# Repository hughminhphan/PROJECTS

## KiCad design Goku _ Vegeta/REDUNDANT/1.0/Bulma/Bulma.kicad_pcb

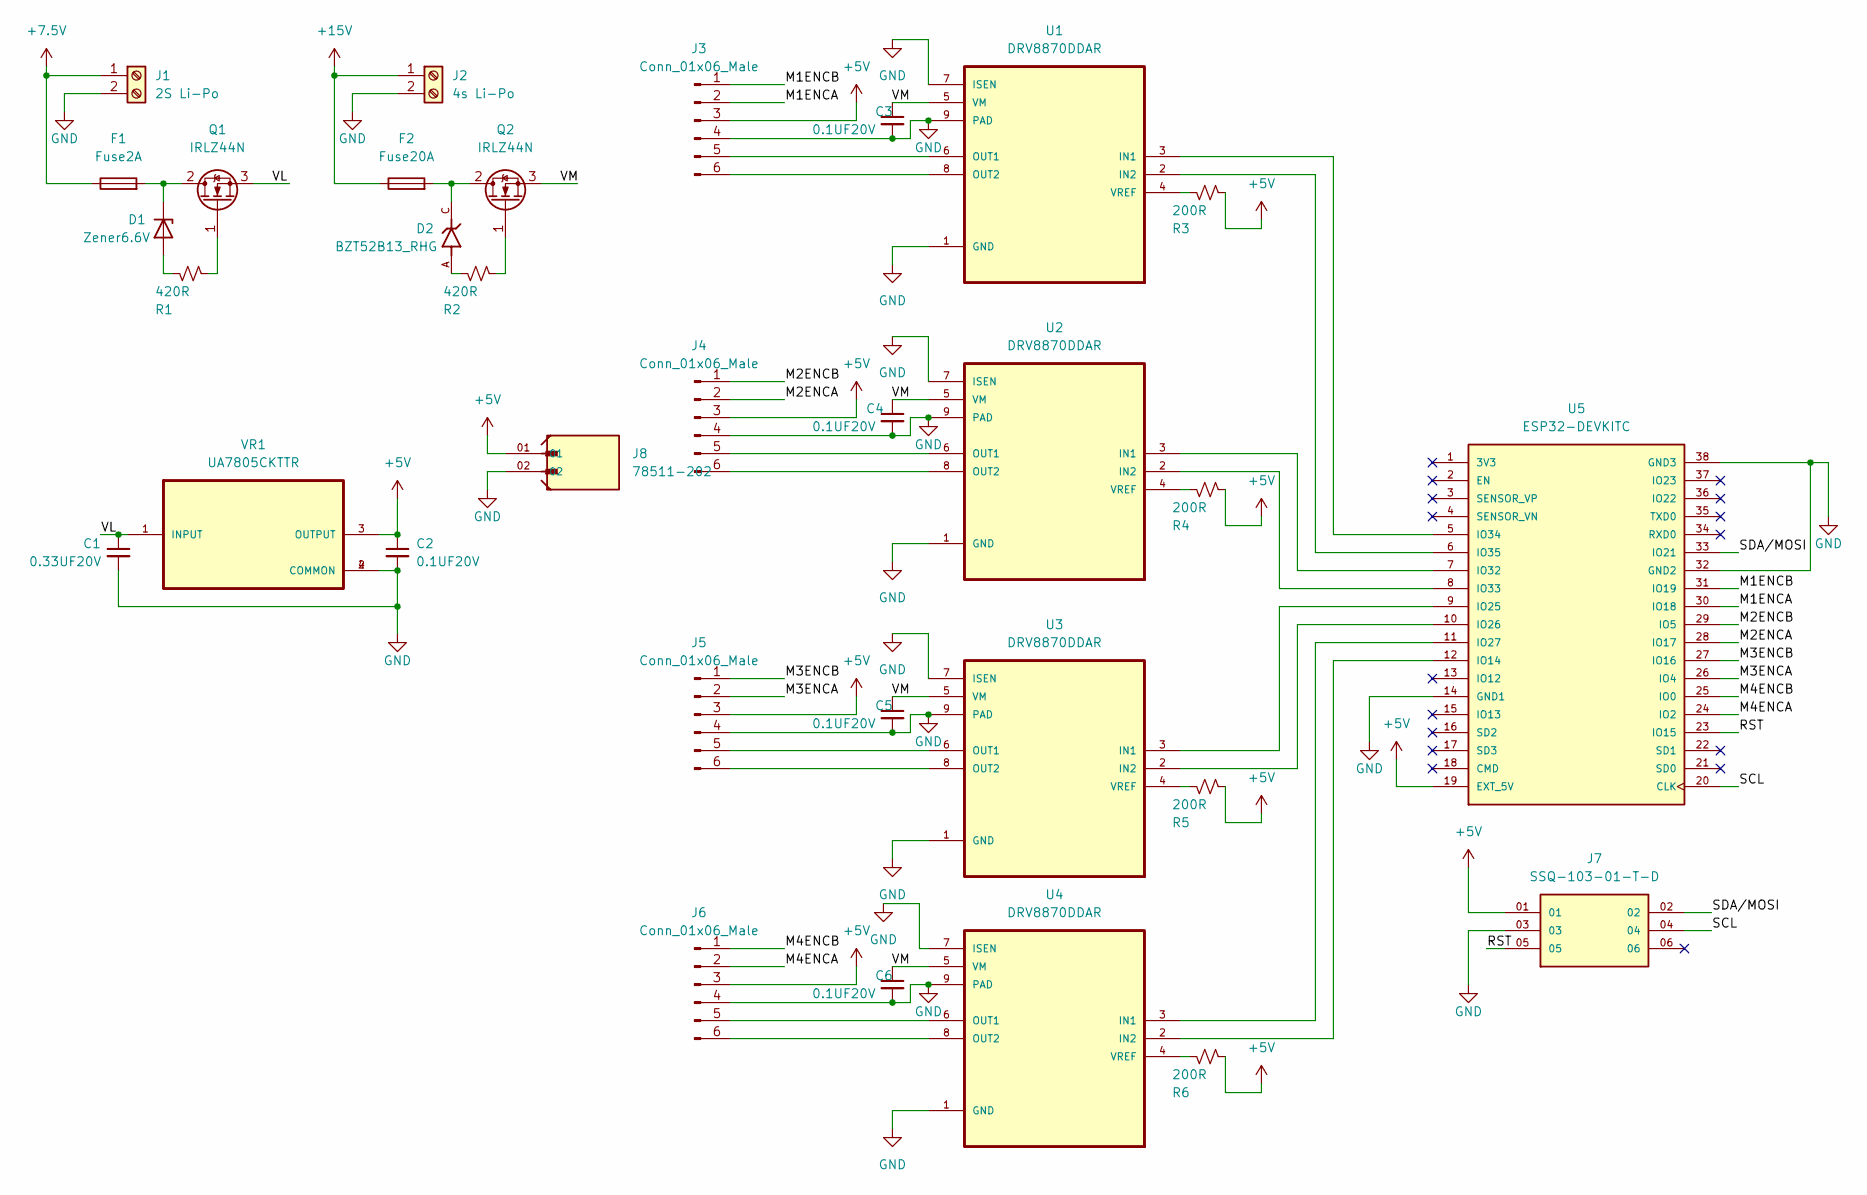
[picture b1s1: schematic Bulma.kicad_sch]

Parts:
C1: 0.33UF20V; C_0201_0603Metric
C2, C3, C4, C5, C6: 0.1UF20V; C_0402_1005Metric
D1: Zener6.6V; SODFL4725X110N
D2: BZT52B13_RHG; DIO_BZT52B13_RHG; PARTREV F15
F1: Fuse2A; FUSC1608X60N
F2: Fuse20A; FUSC3215X85N
J1: 2S Li-Po; 2 Position Wire to Board Terminal Block Horizontal with Boa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
J2: 4s Li-Po; 2 Position Wire to Board Terminal Block Horizontal with Boa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
J3, J5, J6: Conn_01x06_Male; PinSocket_1x06_P2.54mm_Vertical
J4: Conn_01x06_Male; PinHeader_1x06_P2.54mm_Vertical
J7: SSQ-103-01-T-D; SAMTEC_SSQ-103-01-T-D; PARTREV R
J8: 78511-202; AMPHENOL_78511-202; PARTREV DF
Q1, Q2: IRLZ44N; TO-263-2
R1, R2: 420R; R_0805_2012Metric
R3, R4, R5, R6: 200R; R_1206_3216Metric
U1, U2, U3, U4: DRV8870DDAR; VREG_LM5017MR_NOPB
U5: ESP32-DEVKITC; MODULE_ESP32-DEVKITC; PARTREV N/A
VR1: UA7805CKTTR; TO254P1524X483-4N

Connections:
+5V: C2.1, J3.3, J4.3, J5.3, J6.3, J7.01, J8.01, R3.2, R4.2, R5.2, R6.2, U5.19 (EXT_5V), VR1.3 (OUTPUT)
+7.5V: F1.1, J1.1
+15V: F2.1, J2.1
/M1ENCA: J3.2, U5.30 (IO18)
/M1ENCB: J3.1, U5.31 (IO19)
/M2ENCA: J4.2, U5.28 (IO17)
/M2ENCB: J4.1, U5.29 (IO5)
/M3ENCA: J5.2, U5.26 (IO4)
/M3ENCB: J5.1, U5.27 (IO16)
/M4ENCA: J6.2, U5.24 (IO2)
/M4ENCB: J6.1, U5.25 (IO0)
/RST: J7.05, U5.23 (IO15)
/SCL: J7.04, U5.20 (CLK)
/SDA/MOSI: J7.02, U5.33 (IO21)
/VL: C1.1, Q1.3 (S), VR1.1 (INPUT)
/VM: C3.1, C4.1, C5.1, C6.1, Q2.3 (S), U1.5 (VM), U2.5 (VM), U3.5 (VM), U4.5 (VM)
GND: C1.2, C2.2, C3.2, C4.2, C5.2, C6.2, J1.2, J2.2, J3.4, J4.4, J5.4, J6.4, J7.03, J8.02, U1.1 (GND), U1.7 (ISEN), U1.9 (PAD), U2.1 (GND), U2.7 (ISEN), U2.9 (PAD), U3.1 (GND), U3.7 (ISEN), U3.9 (PAD), U4.1 (GND), U4.7 (ISEN), U4.9 (PAD), U5.14 (GND1), U5.32 (GND2), U5.38 (GND3), VR1.2 (COMMON), VR1.4 (COMMON)
unnamed: D1.1 (K), F1.2, Q1.2 (D)
unnamed: D1.2 (A), R1.1
unnamed: D2.A, R2.1
unnamed: D2.C, F2.2, Q2.2 (D)
unnamed: J3.5, U1.6 (OUT1)
unnamed: J3.6, U1.8 (OUT2)
unnamed: J4.5, U2.6 (OUT1)
unnamed: J4.6, U2.8 (OUT2)
unnamed: J5.5, U3.6 (OUT1)
unnamed: J5.6, U3.8 (OUT2)
unnamed: J6.5, U4.6 (OUT1)
unnamed: J6.6, U4.8 (OUT2)
unnamed: Q1.1 (G), R1.2
unnamed: Q2.1 (G), R2.2
unnamed: R3.1, U1.4 (VREF)
unnamed: R4.1, U2.4 (VREF)
unnamed: R5.1, U3.4 (VREF)
unnamed: R6.1, U4.4 (VREF)
unnamed: U1.2 (IN2), U5.6 (IO35)
unnamed: U1.3 (IN1), U5.5 (IO34)
unnamed: U2.2 (IN2), U5.8 (IO33)
unnamed: U2.3 (IN1), U5.7 (IO32)
unnamed: U3.2 (IN2), U5.10 (IO26)
unnamed: U3.3 (IN1), U5.9 (IO25)
unnamed: U4.2 (IN2), U5.12 (IO14)
unnamed: U4.3 (IN1), U5.11 (IO27)

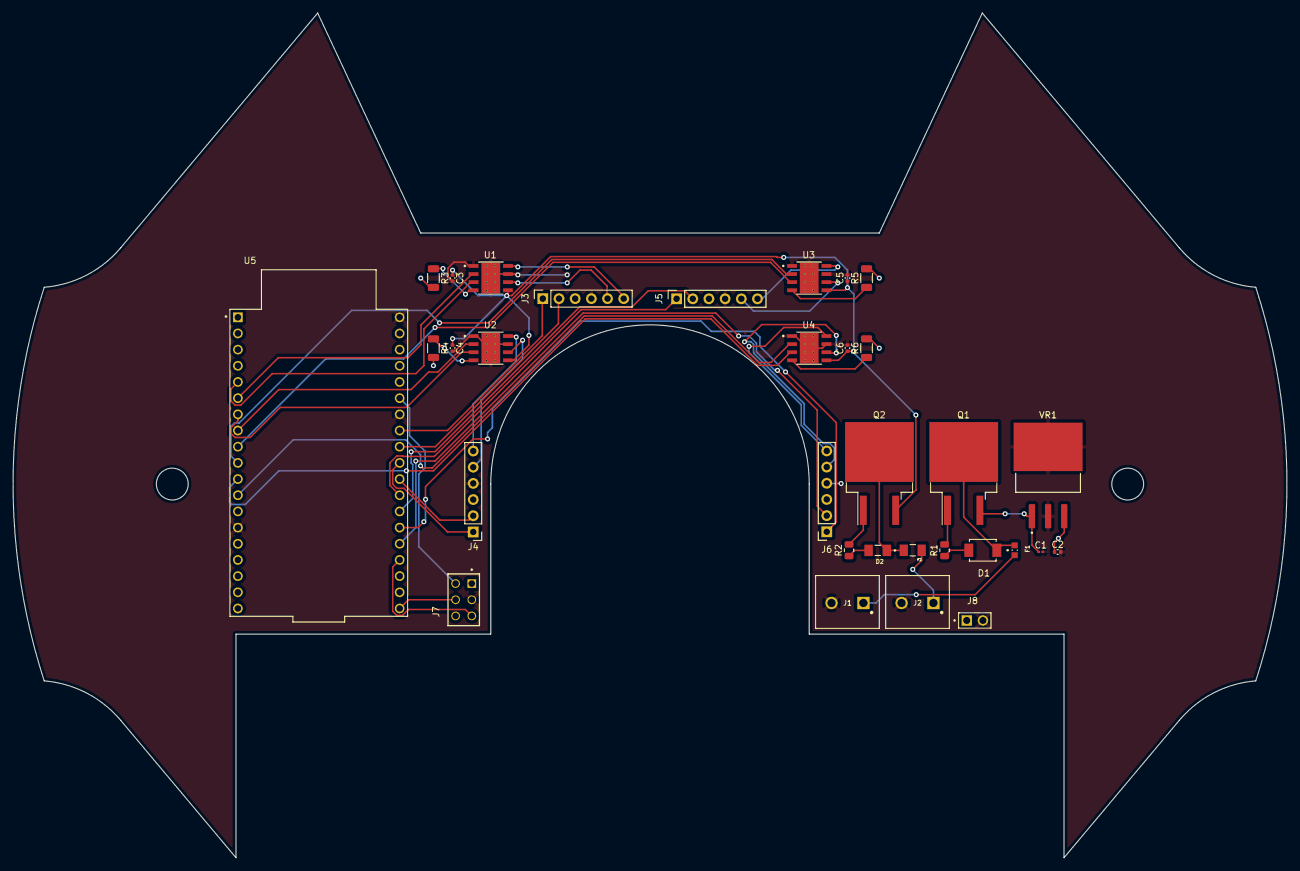
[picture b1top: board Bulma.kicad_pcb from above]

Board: 2 copper layers, 200.0 x 132.6 mm, 32 parts (0 on the bottom side), 43 nets.

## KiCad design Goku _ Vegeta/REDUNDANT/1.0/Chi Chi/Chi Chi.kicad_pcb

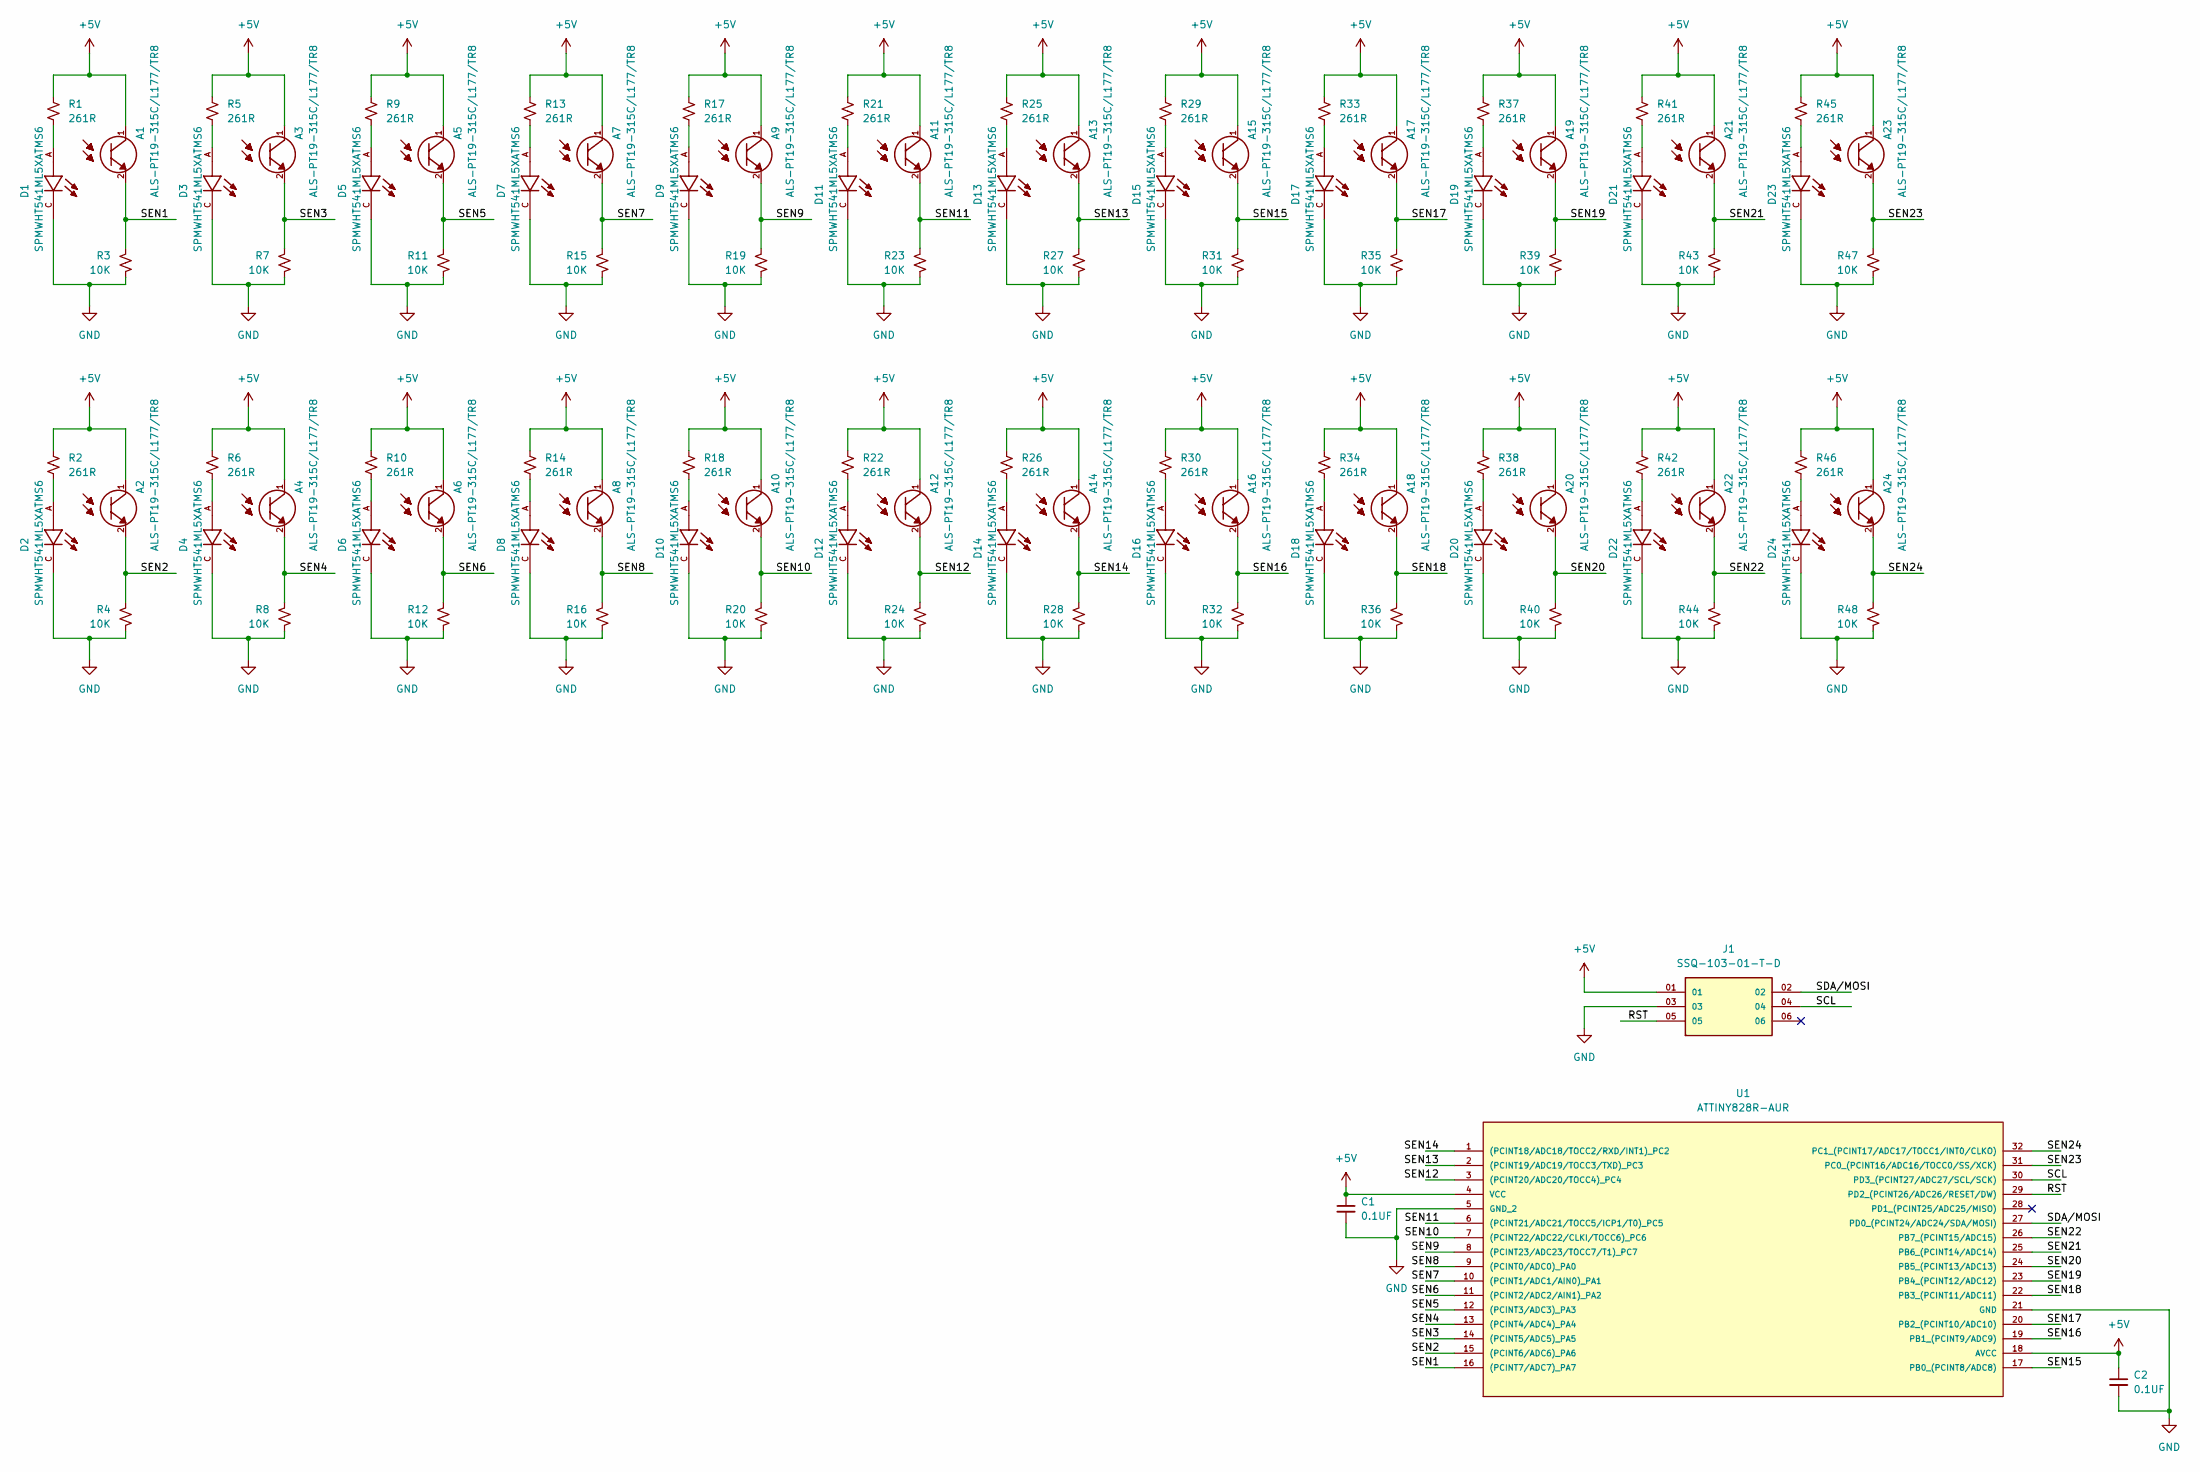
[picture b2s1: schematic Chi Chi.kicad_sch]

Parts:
A1, A2, A3, A4, A5, A6, A7, A8, A9, A10, A11, A12, A13, A14, A15, A16, A17, A18, A19, A20, A21, A22, A23, A24: ALS-PT19-315C/L177/TR8; XDCR_ALS-PT19-315C_L177_TR8; PARTREV 5
C1, C2: 0.1UF; C_0805_2012Metric_Pad1.18x1.45mm_HandSolder
D1, D2, D3, D4, D5, D6, D7, D8, D9, D10, D11, D12, D13, D14, D15, D16, D17, D18, D19, D20, D21, D22, D23, D24: SPMWHT541ML5XATMS6; LED_SPMWHT541MP5WAPKS4; PARTREV 8.3
J1: SSQ-103-01-T-D; SAMTEC_SSQ-103-01-T-D; PARTREV R
R1, R2, R5, R6, R9, R10, R13, R14, R17, R18, R21, R22, R25, R26, R29, R30, R33, R34, R37, R38, R41, R42, R45, R46: 261R; R_0805_2012Metric_Pad1.20x1.40mm_HandSolder
R3, R4, R7, R8, R11, R12, R15, R16, R19, R20, R23, R24, R27, R28, R31, R32, R35, R36, R39, R40, R43, R44, R47, R48: 10K; R_0805_2012Metric_Pad1.20x1.40mm_HandSolder
U1: ATTINY828R-AUR; TQFP32_9X9_MCH; MANUFACTURER_PART_NUMBER ATTINY828R-AUR

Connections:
+5V: A1.1, A2.1, A3.1, A4.1, A5.1, A6.1, A7.1, A8.1, A9.1, A10.1, A11.1, A12.1, A13.1, A14.1, A15.1, A16.1, A17.1, A18.1, A19.1, A20.1, A21.1, A22.1, A23.1, A24.1, C1.1, C2.1, J1.01, R1.1, R2.1, R5.1, R6.1, R9.1, R10.1, R13.1, R14.1, R17.1, R18.1, R21.1, R22.1, R25.1, R26.1, R29.1, R30.1, R33.1, R34.1, R37.1, R38.1, R41.1, R42.1, R45.1, R46.1, U1.4 (VCC), U1.18 (AVCC)
/RST: J1.05, U1.29 (PD2_(PCINT26/ADC26/RESET/DW))
/SCL: J1.04, U1.30 (PD3_(PCINT27/ADC27/SCL/SCK))
/SDA/MOSI: J1.02, U1.27 (PD0_(PCINT24/ADC24/SDA/MOSI))
/SEN1: A1.2, R3.2, U1.16 ((PCINT7/ADC7)_PA7)
/SEN2: A2.2, R4.2, U1.15 ((PCINT6/ADC6)_PA6)
/SEN3: A3.2, R7.2, U1.14 ((PCINT5/ADC5)_PA5)
/SEN4: A4.2, R8.2, U1.13 ((PCINT4/ADC4)_PA4)
/SEN5: A5.2, R11.2, U1.12 ((PCINT3/ADC3)_PA3)
/SEN6: A6.2, R12.2, U1.11 ((PCINT2/ADC2/AIN1)_PA2)
/SEN7: A7.2, R15.2, U1.10 ((PCINT1/ADC1/AIN0)_PA1)
/SEN8: A8.2, R16.2, U1.9 ((PCINT0/ADC0)_PA0)
/SEN9: A9.2, R19.2, U1.8 ((PCINT23/ADC23/TOCC7/T1)_PC7)
/SEN10: A10.2, R20.2, U1.7 ((PCINT22/ADC22/CLKI/TOCC6)_PC6)
/SEN11: A11.2, R23.2, U1.6 ((PCINT21/ADC21/TOCC5/ICP1/T0)_PC5)
/SEN12: A12.2, R24.2, U1.3 ((PCINT20/ADC20/TOCC4)_PC4)
/SEN13: A13.2, R27.2, U1.2 ((PCINT19/ADC19/TOCC3/TXD)_PC3)
/SEN14: A14.2, R28.2, U1.1 ((PCINT18/ADC18/TOCC2/RXD/INT1)_PC2)
/SEN15: A15.2, R31.2, U1.17 (PB0_(PCINT8/ADC8))
/SEN16: A16.2, R32.2, U1.19 (PB1_(PCINT9/ADC9))
/SEN17: A17.2, R35.2, U1.20 (PB2_(PCINT10/ADC10))
/SEN18: A18.2, R36.2, U1.22 (PB3_(PCINT11/ADC11))
/SEN19: A19.2, R39.2, U1.23 (PB4_(PCINT12/ADC12))
/SEN20: A20.2, R40.2, U1.24 (PB5_(PCINT13/ADC13))
/SEN21: A21.2, R43.2, U1.25 (PB6_(PCINT14/ADC14))
/SEN22: A22.2, R44.2, U1.26 (PB7_(PCINT15/ADC15))
/SEN23: A23.2, R47.2, U1.31 (PC0_(PCINT16/ADC16/TOCC0/SS/XCK))
/SEN24: A24.2, R48.2, U1.32 (PC1_(PCINT17/ADC17/TOCC1/INT0/CLKO))
GND: C1.2, C2.2, D1.C, D2.C, D3.C, D4.C, D5.C, D6.C, D7.C, D8.C, D9.C, D10.C, D11.C, D12.C, D13.C, D14.C, D15.C, D16.C, D17.C, D18.C, D19.C, D20.C, D21.C, D22.C, D23.C, D24.C, J1.03, R3.1, R4.1, R7.1, R8.1, R11.1, R12.1, R15.1, R16.1, R19.1, R20.1, R23.1, R24.1, R27.1, R28.1, R31.1, R32.1, R35.1, R36.1, R39.1, R40.1, R43.1, R44.1, R47.1, R48.1, U1.5 (GND_2), U1.21 (GND)
unnamed: D1.A, R1.2
unnamed: D2.A, R2.2
unnamed: D3.A, R5.2
unnamed: D4.A, R6.2
unnamed: D5.A, R9.2
unnamed: D6.A, R10.2
unnamed: D7.A, R13.2
unnamed: D8.A, R14.2
unnamed: D9.A, R17.2
unnamed: D10.A, R18.2
unnamed: D11.A, R21.2
unnamed: D12.A, R22.2
unnamed: D13.A, R25.2
unnamed: D14.A, R26.2
unnamed: D15.A, R29.2
unnamed: D16.A, R30.2
unnamed: D17.A, R33.2
unnamed: D18.A, R34.2
unnamed: D19.A, R37.2
unnamed: D20.A, R38.2
unnamed: D21.A, R41.2
unnamed: D22.A, R42.2
unnamed: D23.A, R45.2
unnamed: D24.A, R46.2

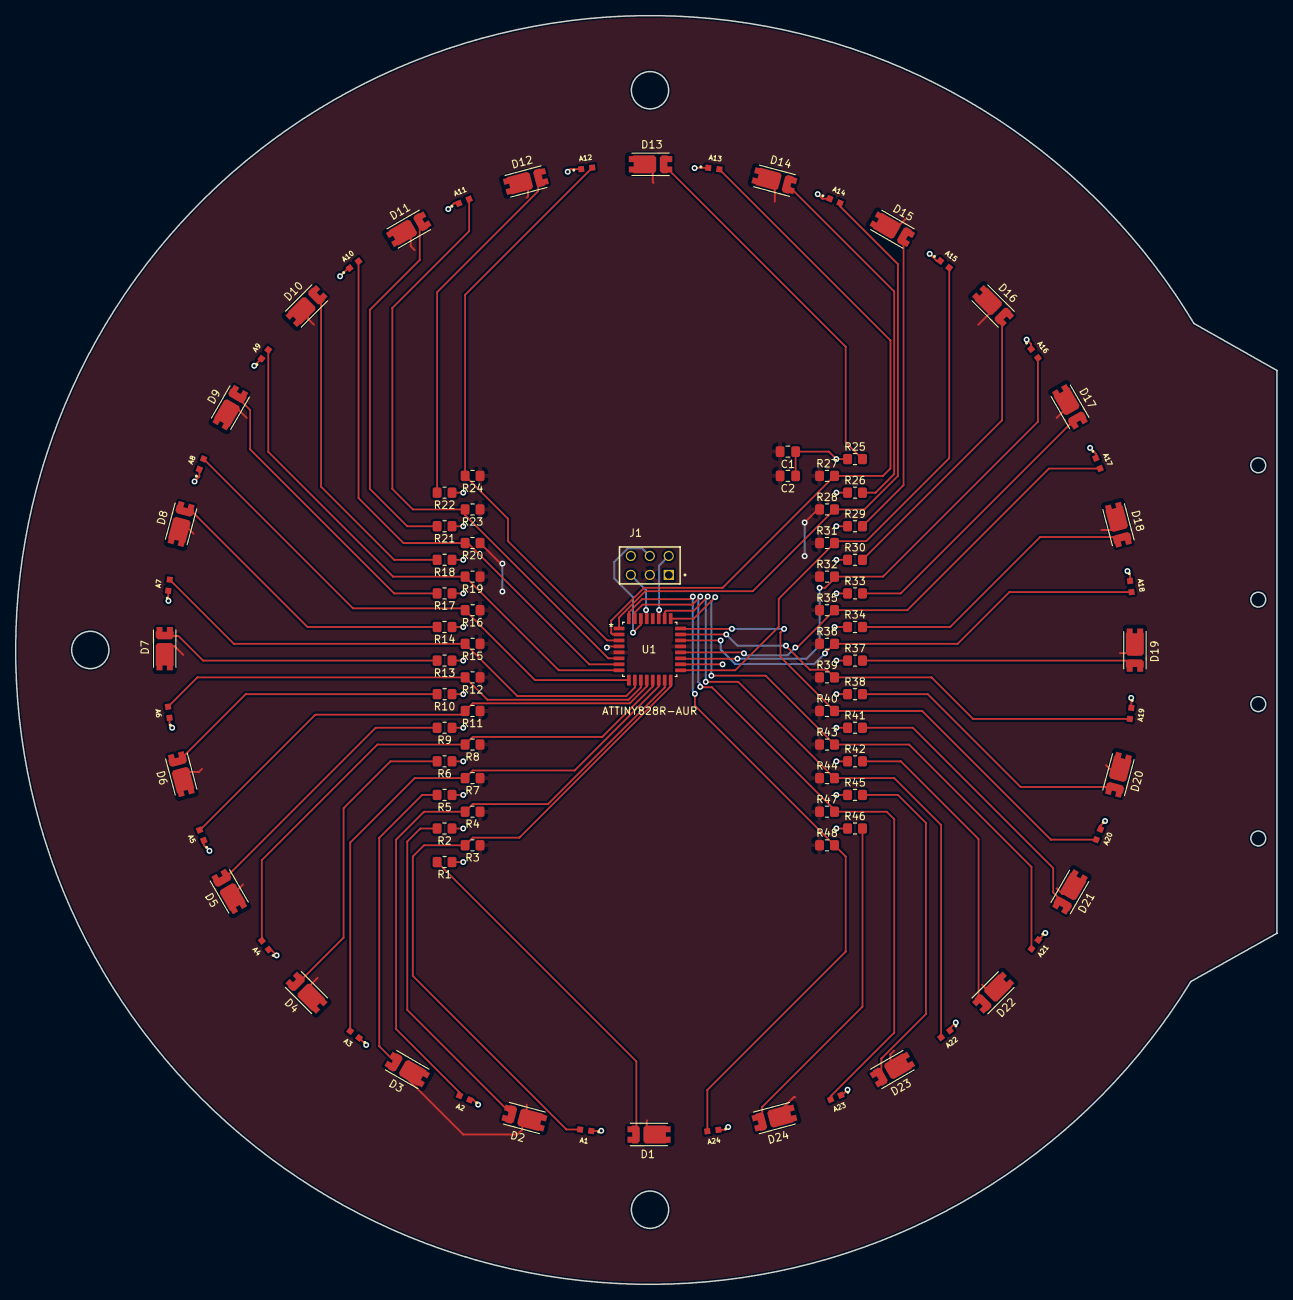
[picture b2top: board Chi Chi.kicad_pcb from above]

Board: 2 copper layers, 169.0 x 170.0 mm, 100 parts (0 on the bottom side), 53 nets.

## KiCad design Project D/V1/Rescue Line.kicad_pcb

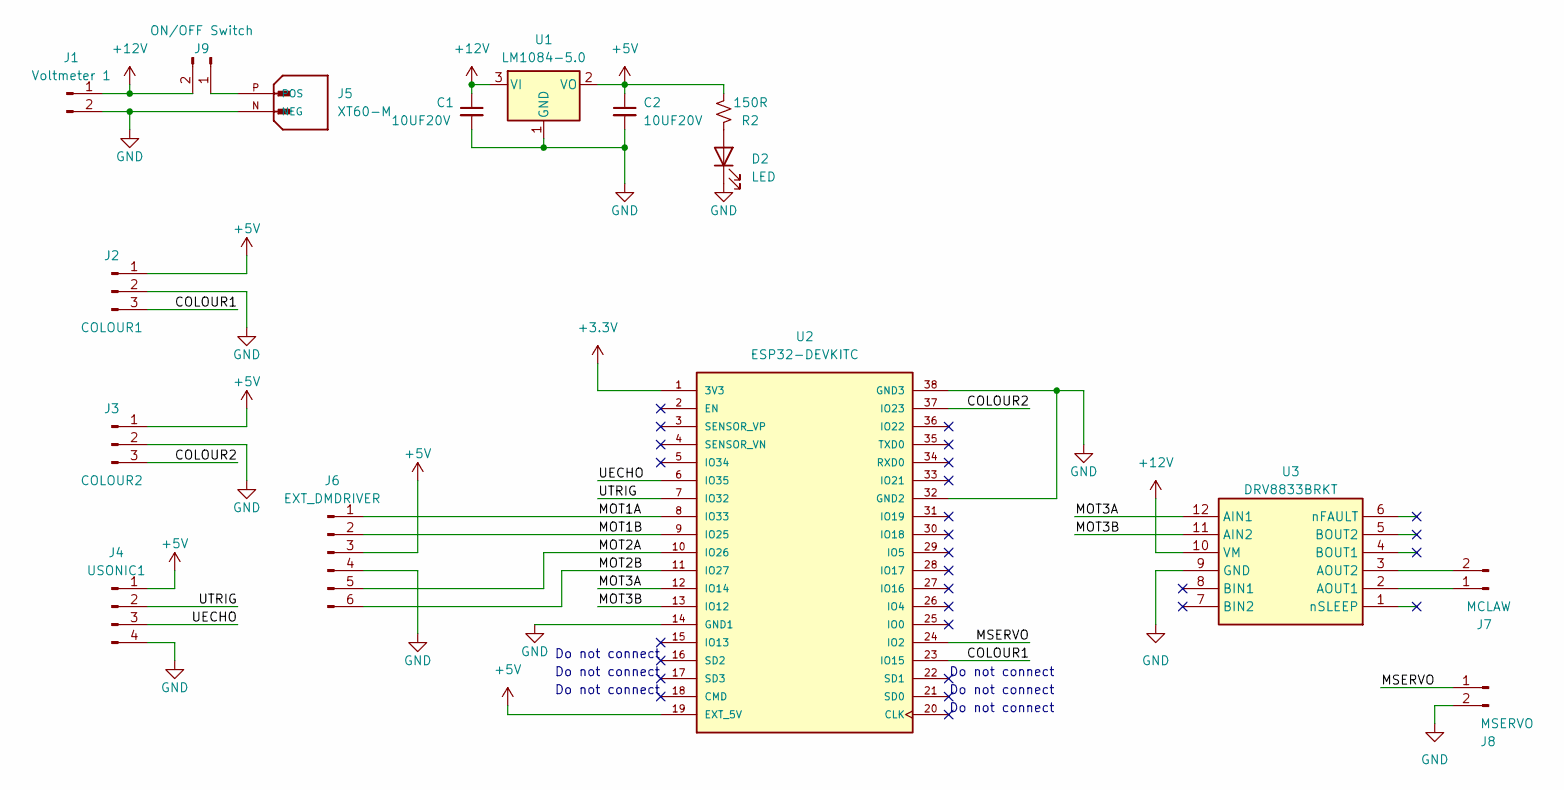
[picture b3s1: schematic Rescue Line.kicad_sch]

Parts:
C1, C2: 10UF20V; C_0805_2012Metric
D2: LED; LED_0603_1608Metric
J1: Voltmeter 1; PinHeader_1x02_P2.54mm_Vertical
J2: COLOUR1; PinSocket_1x03_P2.54mm_Vertical
J3: COLOUR2; PinSocket_1x03_P2.54mm_Vertical
J4: USONIC1; PinHeader_1x04_P2.54mm_Vertical
J5: XT60-M; AMASS_XT60-M; PARTREV V1.2
J6: EXT_DMDRIVER
J7: MCLAW; PinHeader_1x02_P2.54mm_Vertical
J8: MSERVO; PinHeader_1x02_P2.54mm_Vertical
J9: ON/OFF Switch; PinHeader_1x02_P2.54mm_Vertical
R2: 150R; R_0805_2012Metric
U1: LM1084-5.0; TO-263-3_TabPin2
U2: ESP32-DEVKITC; MODULE_ESP32-DEVKITC; PARTREV N/A
U3: DRV8833BRKT

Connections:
+3.3V: U2.1 (3V3)
+5V: C2.1, J2.1, J3.1, J4.1, J6.3, R2.2, U1.2 (VO), U2.19 (EXT_5V)
+12V: C1.1, J1.1, J9.2, U1.3 (VI), U3.10 (VM)
/COLOUR1: J2.3, U2.23 (IO15)
/COLOUR2: J3.3, U2.37 (IO23)
/MOT1A: J6.1, U2.8 (IO33)
/MOT1B: J6.2, U2.9 (IO25)
/MOT2A: J6.5, U2.10 (IO26)
/MOT2B: J6.6, U2.11 (IO27)
/MOT3A: U2.12 (IO14), U3.12 (AIN1)
/MOT3B: U2.13 (IO12), U3.11 (AIN2)
/MSERVO: J8.1, U2.24 (IO2)
/UECHO: J4.3, U2.6 (IO35)
/UTRIG: J4.2, U2.7 (IO32)
GND: C1.2, C2.2, D2.1 (K), J1.2, J2.2, J3.2, J4.4, J5.N (NEG), J6.4, J8.2, U1.1 (GND), U2.14 (GND1), U2.32 (GND2), U2.38 (GND3), U3.9 (GND)
unnamed: D2.2 (A), R2.1
unnamed: J5.P (POS), J9.1
unnamed: J7.1, U3.2 (AOUT1)
unnamed: J7.2, U3.3 (AOUT2)

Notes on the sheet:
Do not connect

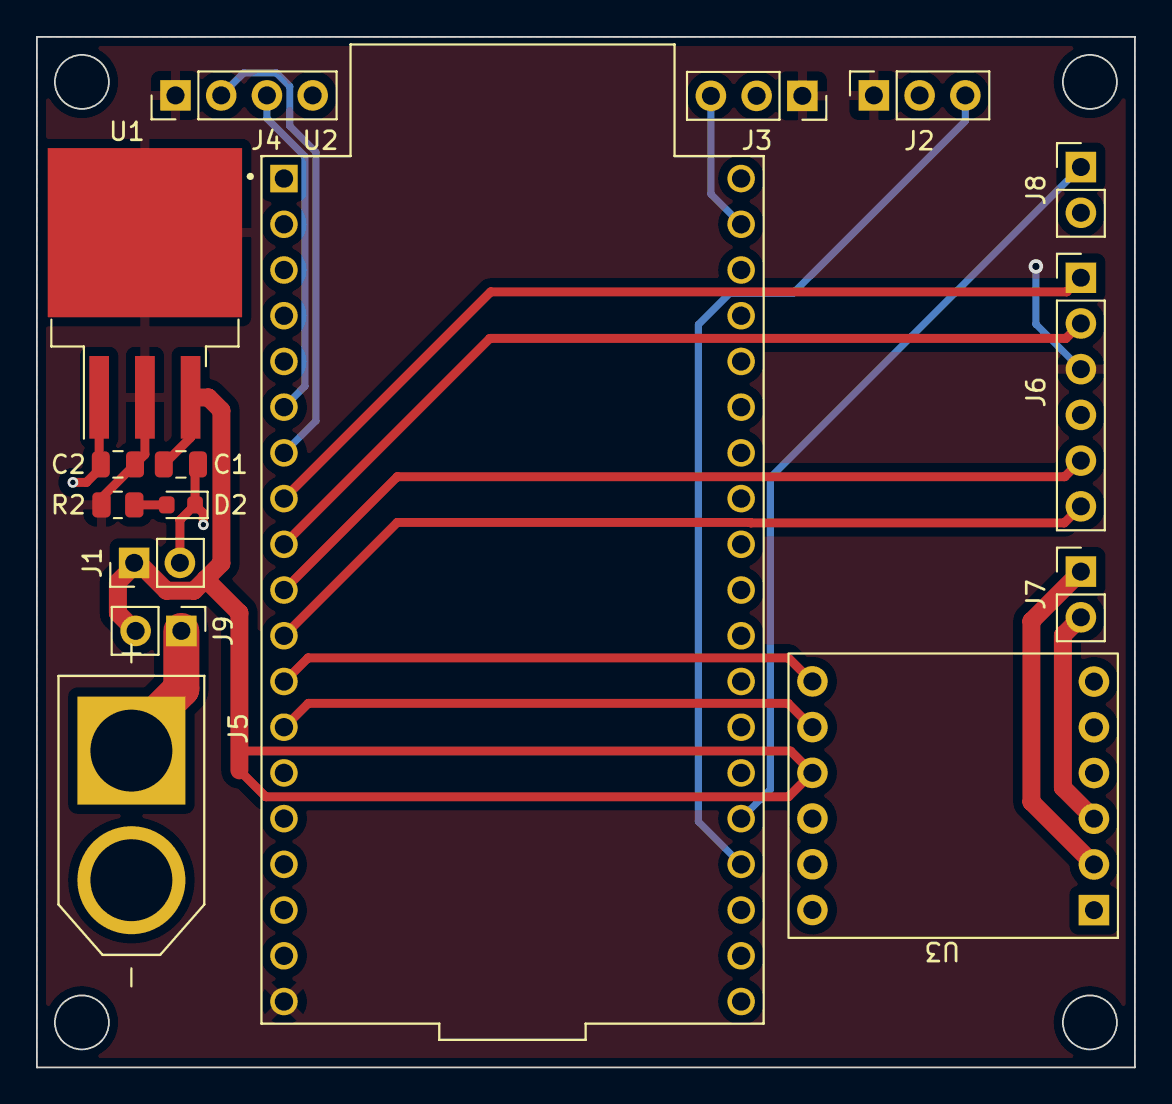
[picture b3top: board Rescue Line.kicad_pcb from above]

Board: 2 copper layers, 61.0 x 57.2 mm, 16 parts (0 on the bottom side), 18 nets.

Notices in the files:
parts and their libraries:
COPYRIGHT: Copyright (C) 2018 Accelerated Designs. All rights reserved
